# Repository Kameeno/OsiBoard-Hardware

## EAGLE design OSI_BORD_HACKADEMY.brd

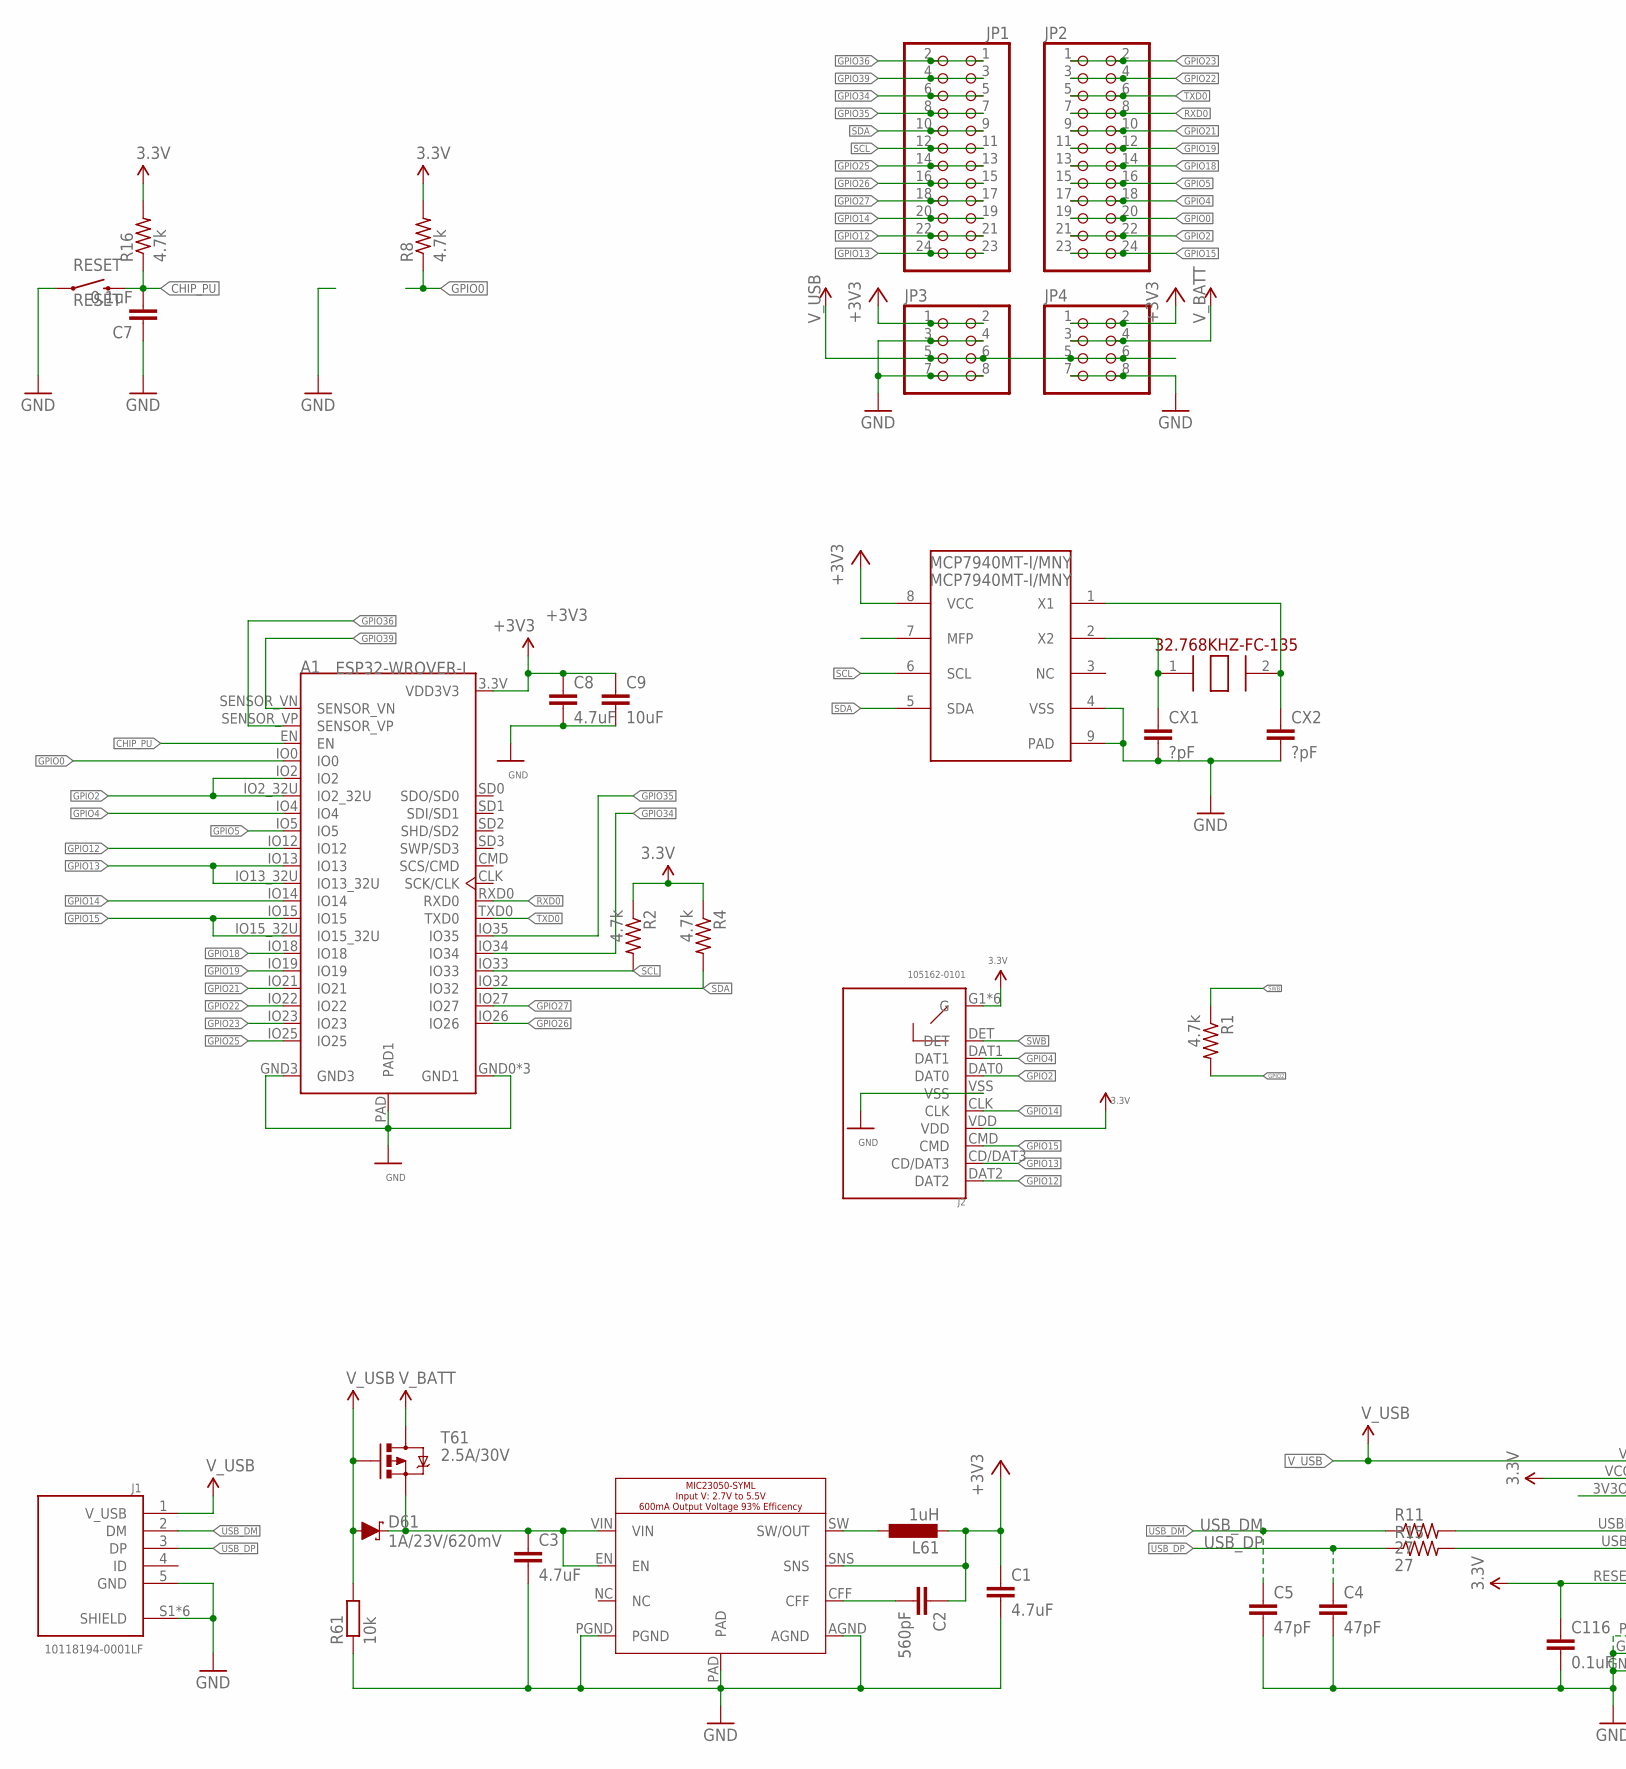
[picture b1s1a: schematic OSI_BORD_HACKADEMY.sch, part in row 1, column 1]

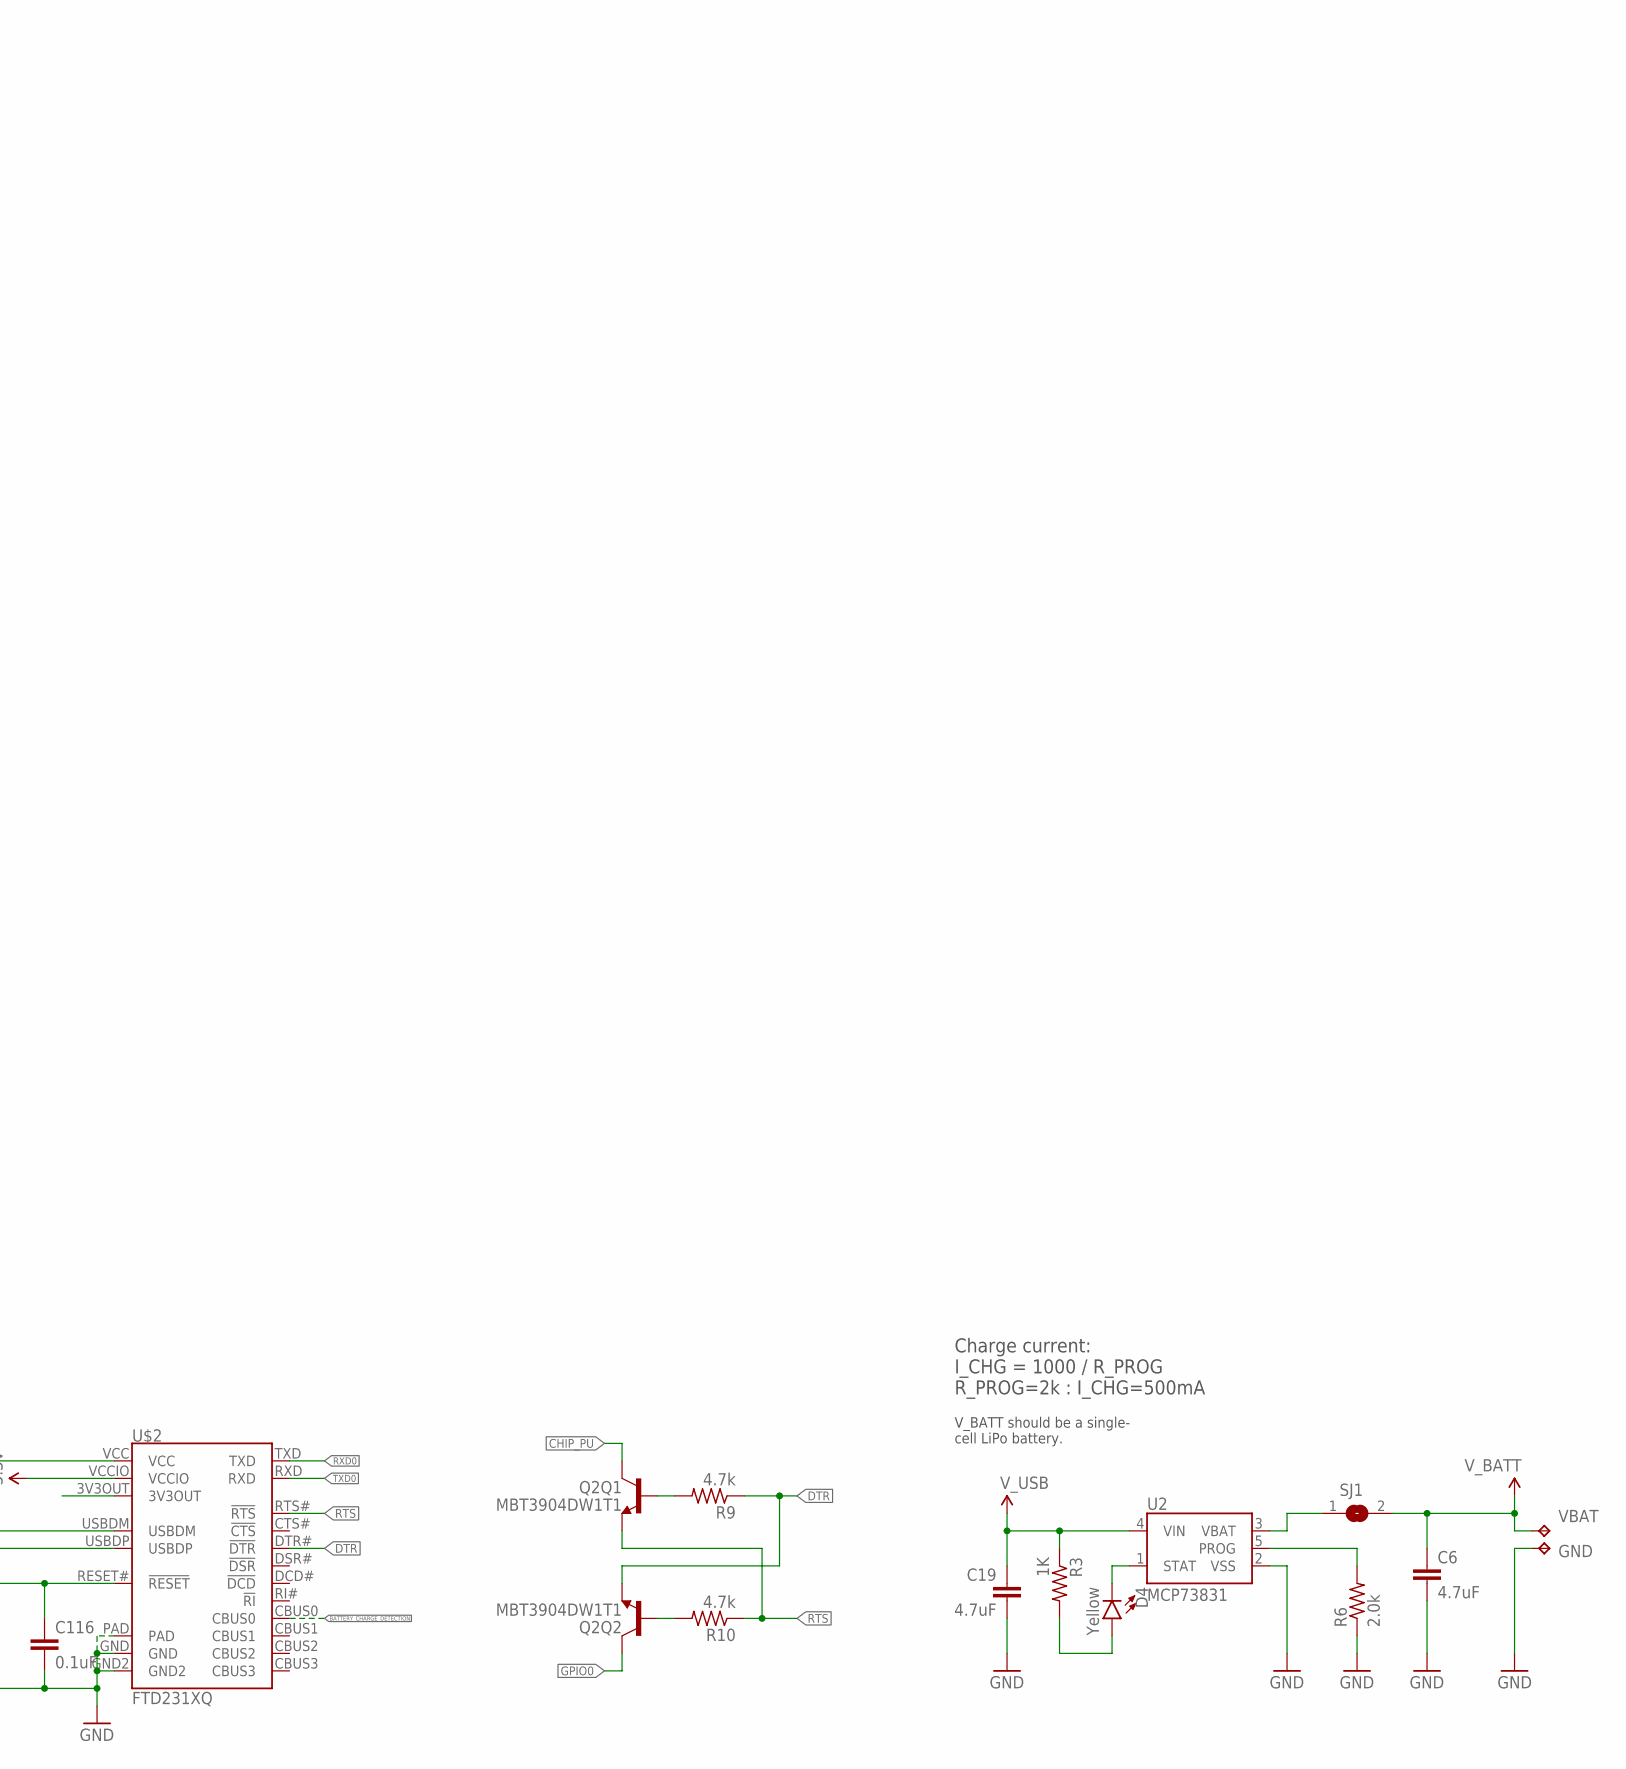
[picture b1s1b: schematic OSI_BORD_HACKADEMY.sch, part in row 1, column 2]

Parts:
A1: ESP32-WROVER-I; XCVR_ESP32-WROVER-I
C1, C3, C6, C8, C19: 4.7uF; C0402
C2: 560pF; C0402
C4, C5: 47pF; C0402
C7, C116: 0.1uF; C0402
C9: 10uF; C0402
CX1, CX2: ?pF; C0402
D4: Yellow; LED-0603
D61: 1A/23V/620mV; SOD-323
GND: TPB1,27; B1,27
J1: 10118194-0001LF; AMPHENOL_10118194-0001LF
J2: 105162-0101; MOLEX_105162-0101
JP1, JP2: PINHD-2X12; 2X12
JP3, JP4: PINHD-2X4; 2X04
L61: 1uH; VLS3015
MCP7940MT-I/MNY: MCP7940MT-I/MNY; TDFN-8
Q2: MBT3904DW1T1; SC70-6
R1, R2, R4, R8, R9, R10, R16: 4.7k; R0402
R3: 1K; R0402
R6: 2.0k; R0402
R11, R15: 27; R0402
R61: 10k; R0402
RESET: RESET; TACTILE_SWITCH_SMD_4.6X2.8MM
SJ1: SJ
T61: 2.5A/30V; SOT23-3@1
U2: MCP73831; SOT23-5
U$1: MIC23050-SYML; DFN8G-0.5-2X2MM
U$2: FTD231XQ; QFN-20
U$3: 32.768KHZ-FC-135
VBAT: TPB1,27; B1,27

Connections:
+3V3: A1.3.3V (VDD3V3), C1.1, C2.1, C8.1, C9.1, C116.1, J2.G1 (G), J2.G2 (G), J2.G3 (G), J2.G4 (G), J2.SH1 (G), J2.SH2 (G), J2.VDD, JP3.1, JP3.2, JP4.1, JP4.2, L61.P$2 (2), MCP7940MT-I/MNY.8 (VCC), R2.1, R4.1, R8.2, R16.2, U$1.SNS, U$2.RESET# (!RESET), U$2.VCCIO
BATTERY_CHARGE_DETECTION: U$2.CBUS0
CHIP_PU: A1.EN, C7.2, Q2.3 (C), R16.1, RESET.3 (2), RESET.4 (2)
DTR: Q2.1 (E), R9.1, U$2.DTR# (!DTR)
GND: A1.GND0 (GND1), A1.GND1, A1.GND2 (GND1), A1.GND3, A1.PAD (PAD1), C1.2, C3.2, C4.2, C5.2, C6.2, C7.1, C8.2, C9.2, C19.2, C116.2, CX1.2, CX2.2, GND.TP, J1.5 (GND), J1.S1 (SHIELD), J1.S2 (SHIELD), J1.S3 (SHIELD), J1.S4 (SHIELD), J1.S5 (SHIELD), J1.S6 (SHIELD), J2.VSS, JP3.3, JP3.4, JP3.7, JP3.8, JP4.7, JP4.8, MCP7940MT-I/MNY.4 (VSS), MCP7940MT-I/MNY.9 (PAD), R6.1, R61.1, RESET.1, RESET.2 (1), U2.2 (VSS), U$1.AGND, U$1.PAD, U$1.PGND, U$2.GND, U$2.GND2, U$2.PAD
GPIO0: A1.IO0, JP2.19, JP2.20, Q2.6 (C), R8.1
GPIO2: A1.IO2, A1.IO2_32U, J2.DAT0, JP2.21, JP2.22, R1.2
GPIO4: A1.IO4, J2.DAT1, JP2.17, JP2.18
GPIO5: A1.IO5, JP2.15, JP2.16
GPIO12: A1.IO12, J2.DAT2, JP1.21, JP1.22
GPIO13: A1.IO13, A1.IO13_32U, J2.CD/DAT3, JP1.23, JP1.24
GPIO14: A1.IO14, J2.CLK, JP1.19, JP1.20
GPIO15: A1.IO15, A1.IO15_32U, J2.CMD, JP2.23, JP2.24
GPIO18: A1.IO18, JP2.13, JP2.14
GPIO19: A1.IO19, JP2.11, JP2.12
GPIO21: A1.IO21, JP2.9, JP2.10
GPIO22: A1.IO22, JP2.3, JP2.4
GPIO23: A1.IO23, JP2.1, JP2.2
GPIO25: A1.IO25, JP1.13, JP1.14
GPIO26: A1.IO26, JP1.15, JP1.16
GPIO27: A1.IO27, JP1.17, JP1.18
GPIO34: A1.IO34, JP1.5, JP1.6
GPIO35: A1.IO35, JP1.7, JP1.8
GPIO36: A1.SENSOR_VP, JP1.1, JP1.2
GPIO39: A1.SENSOR_VN, JP1.3, JP1.4
unnamed: L61.P$1 (1), U$1.SW (SW/OUT)
unnamed: D4.C, U2.1 (STAT)
unnamed: SJ1.1, U2.3 (VBAT)
unnamed: C2.2, U$1.CFF
unnamed: C3.1, D61.C, T61.2 (S), U$1.EN, U$1.VIN
unnamed: CX1.1, MCP7940MT-I/MNY.2 (X2), U$3.1 (1.XIN)
unnamed: CX2.1, MCP7940MT-I/MNY.1 (X1), U$3.2 (2.XIN)
unnamed: R6.2, U2.5 (PROG)
unnamed: D4.A, R3.2
unnamed: Q2.5 (B), R9.2
unnamed: Q2.2 (B), R10.2
unnamed: R11.2, U$2.USBDM
unnamed: R15.2, U$2.USBDP
RTS: Q2.4 (E), R10.1, U$2.RTS# (!RTS)
RXD0: A1.RXD0, JP2.7, JP2.8, U$2.TXD
SCL: A1.IO33, JP1.11, JP1.12, MCP7940MT-I/MNY.6 (SCL), R2.2
SDA: A1.IO32, JP1.9, JP1.10, MCP7940MT-I/MNY.5 (SDA), R4.2
SWB: J2.DET, R1.1
TXD0: A1.TXD0, JP2.5, JP2.6, U$2.RXD
USB_DM: C5.1, J1.2 (DM), R11.1
USB_DP: C4.1, J1.3 (DP), R15.1
V_BATT: C6.1, JP4.3, JP4.4, SJ1.2, T61.3 (D), VBAT.TP
V_USB: C19.1, D61.A, J1.1 (V_USB), JP3.5, JP3.6, JP4.5, JP4.6, R3.1, R61.2, T61.1 (G), U2.4 (VIN), U$2.VCC

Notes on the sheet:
V_BATT should be a single- cell LiPo battery.
Charge current: I_CHG = 1000 / R_PROG R_PROG=2k : I_CHG=500mA

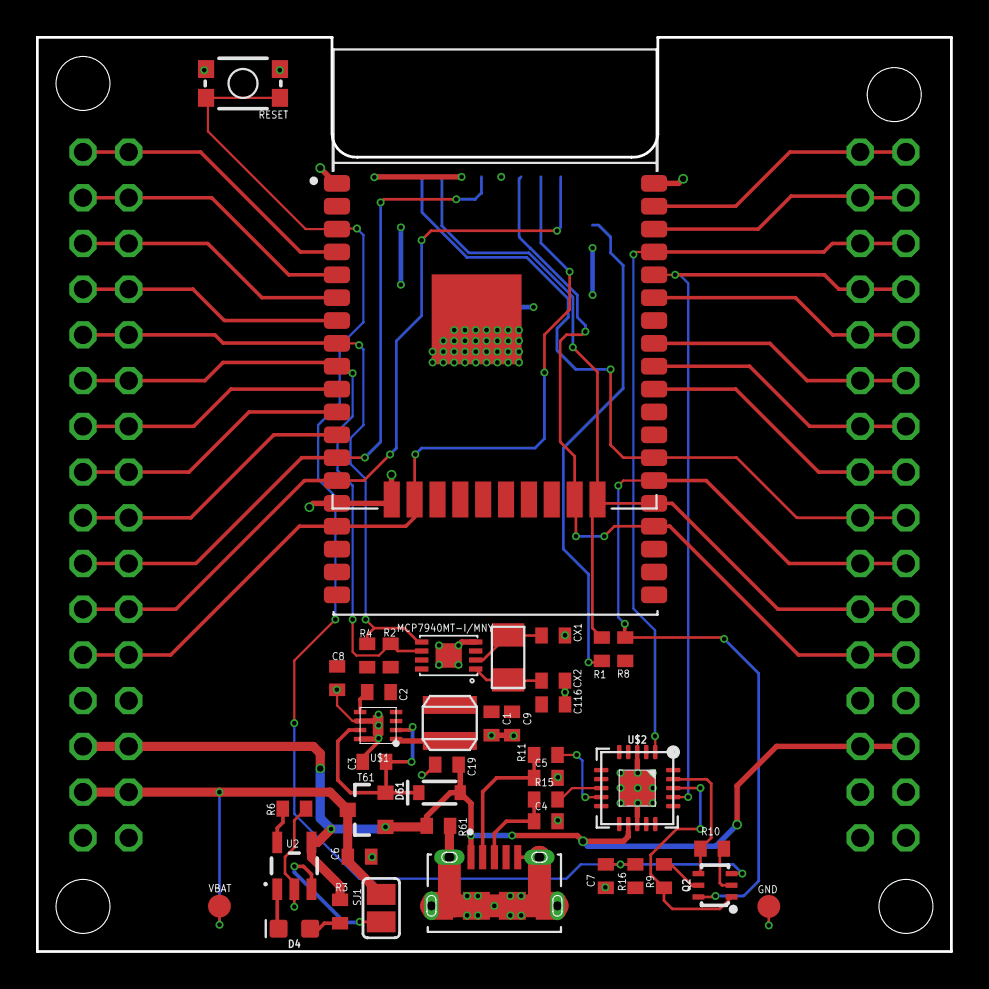
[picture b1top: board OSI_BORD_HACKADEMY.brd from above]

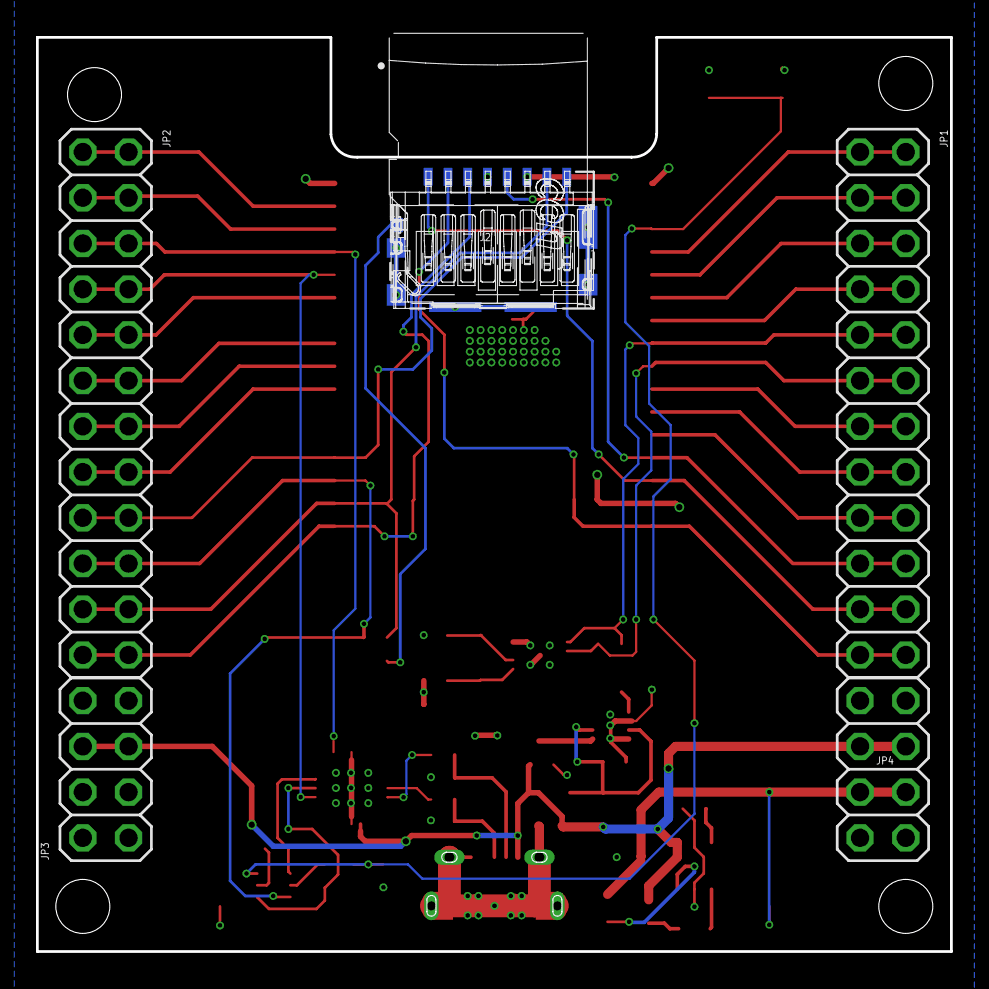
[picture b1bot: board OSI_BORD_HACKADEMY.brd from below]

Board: 2 copper layers, 50.8 x 50.8 mm, 46 parts (5 on the bottom side), 47 nets.

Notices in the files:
parts and their libraries:
SparkFun-LED: Licensing: Creative Commons ShareAlike 4.0 International - https://creativecommons.org/licenses/by-sa/4.0
